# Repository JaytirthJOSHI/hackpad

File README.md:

Ok, I'm makeing a HackPad from by following the Hack Club's HackPad tutorial at hackpad.hackclub.com. I'm uploading a picture of what my HackPad currently looks like in Fusion 360. 

link: https://hc-cdn.hel1.your-objectstorage.com/s/v3/274e45fef3fa933dffc1ed8951e65266f0deea98_screenshot_2025-11-09_at_1.37.17___pm.png

ill need funding for the pcb and im expecting a kit for the rest :)

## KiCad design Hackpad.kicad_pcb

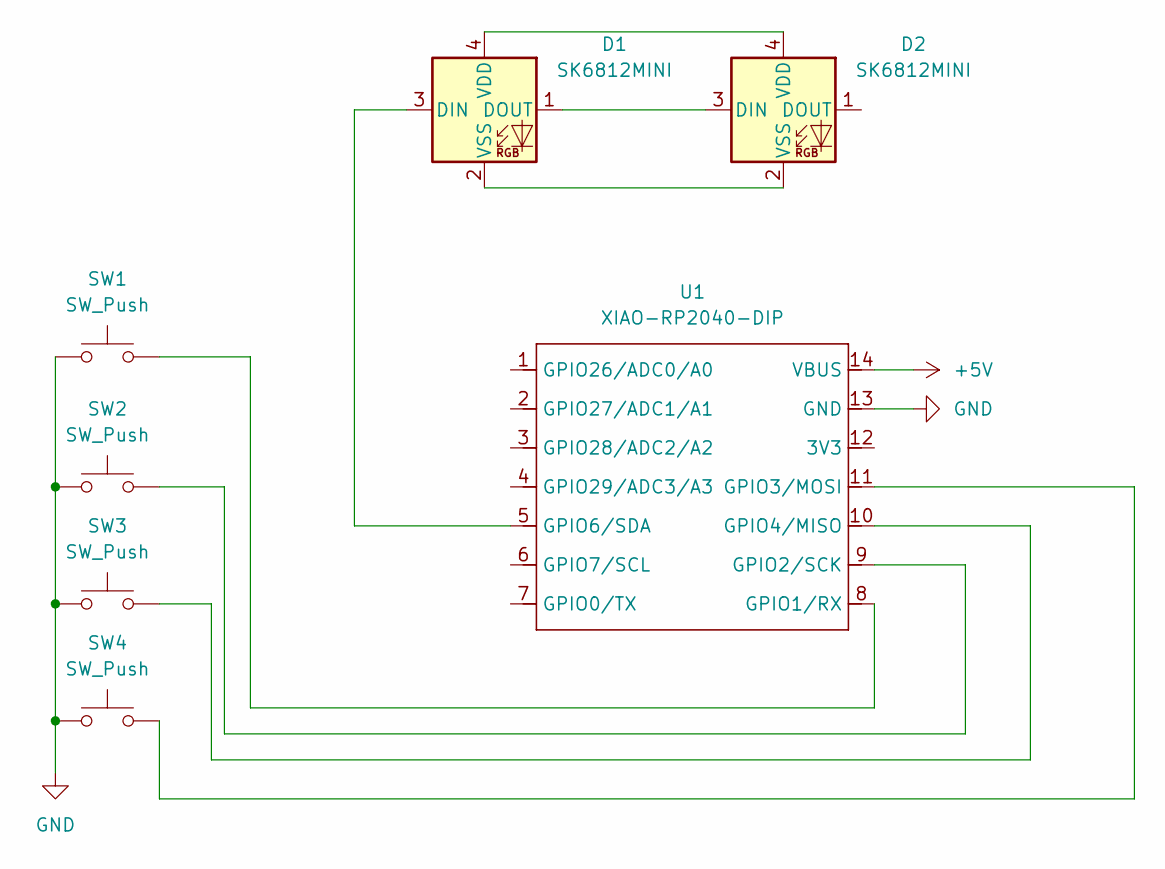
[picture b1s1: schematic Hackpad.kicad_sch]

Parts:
D1, D2: SK6812MINI; LED_SK6812MINI_PLCC4_3.5x3.5mm_P1.75mm
SW1, SW2, SW3, SW4: SW_Push; SW_Cherry_MX_1.00u_PCB
U1: XIAO-RP2040-DIP; XIAO-RP2350-DIP

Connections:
+5V: U1.14 (VBUS)
GND: SW1.1, SW2.1, SW3.1, SW4.1, U1.13 (GND)
unnamed: D1.3 (DIN), U1.5 (GPIO6/SDA)
unnamed: D1.1 (DOUT), D2.3 (DIN)
unnamed: D1.4 (VDD), D2.4 (VDD)
unnamed: D1.2 (VSS), D2.2 (VSS)
unnamed: SW1.2, U1.8 (GPIO1/RX)
unnamed: SW2.2, U1.9 (GPIO2/SCK)
unnamed: SW4.2, U1.11 (GPIO3/MOSI)
unnamed: SW3.2, U1.10 (GPIO4/MISO)

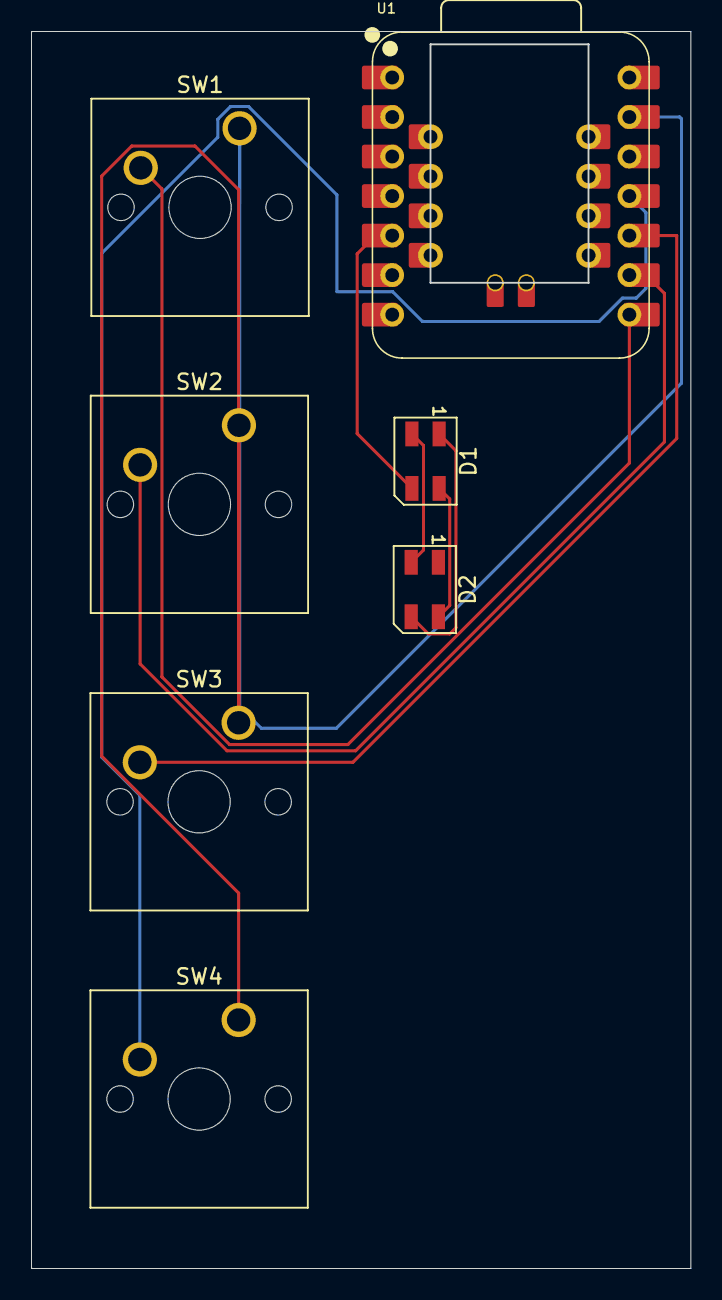
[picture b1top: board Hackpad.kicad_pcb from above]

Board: 2 copper layers, 42.4 x 79.5 mm, 7 parts (0 on the bottom side), 9 nets.

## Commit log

2025-11-02 file management
2025-11-02 Renameing folder sorry lol
2025-11-09 forgot to do some cummit
2025-11-12 Add HackPad tutorial progress and funding request
2025-11-12 Fix typos in README.md HackPad description
    Corrected typos and improved clarity in the HackPad description.
